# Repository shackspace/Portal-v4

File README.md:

Portal v4
=========

Portal v4 is the latest version of the shackspace [portal](https://github.com/shackspace/portal-v4). It controls access to shackspace through the ssh keys of the key members. Portal v4 is a more enhanced version and makes use of the Rasperry Pis GPIO pins. Also all python scripts are now updated from python 2.x to python 3.x.

Documentation for the setup is in `doc/setup.md`. The hardware setup is described in 'doc/hardware.md'

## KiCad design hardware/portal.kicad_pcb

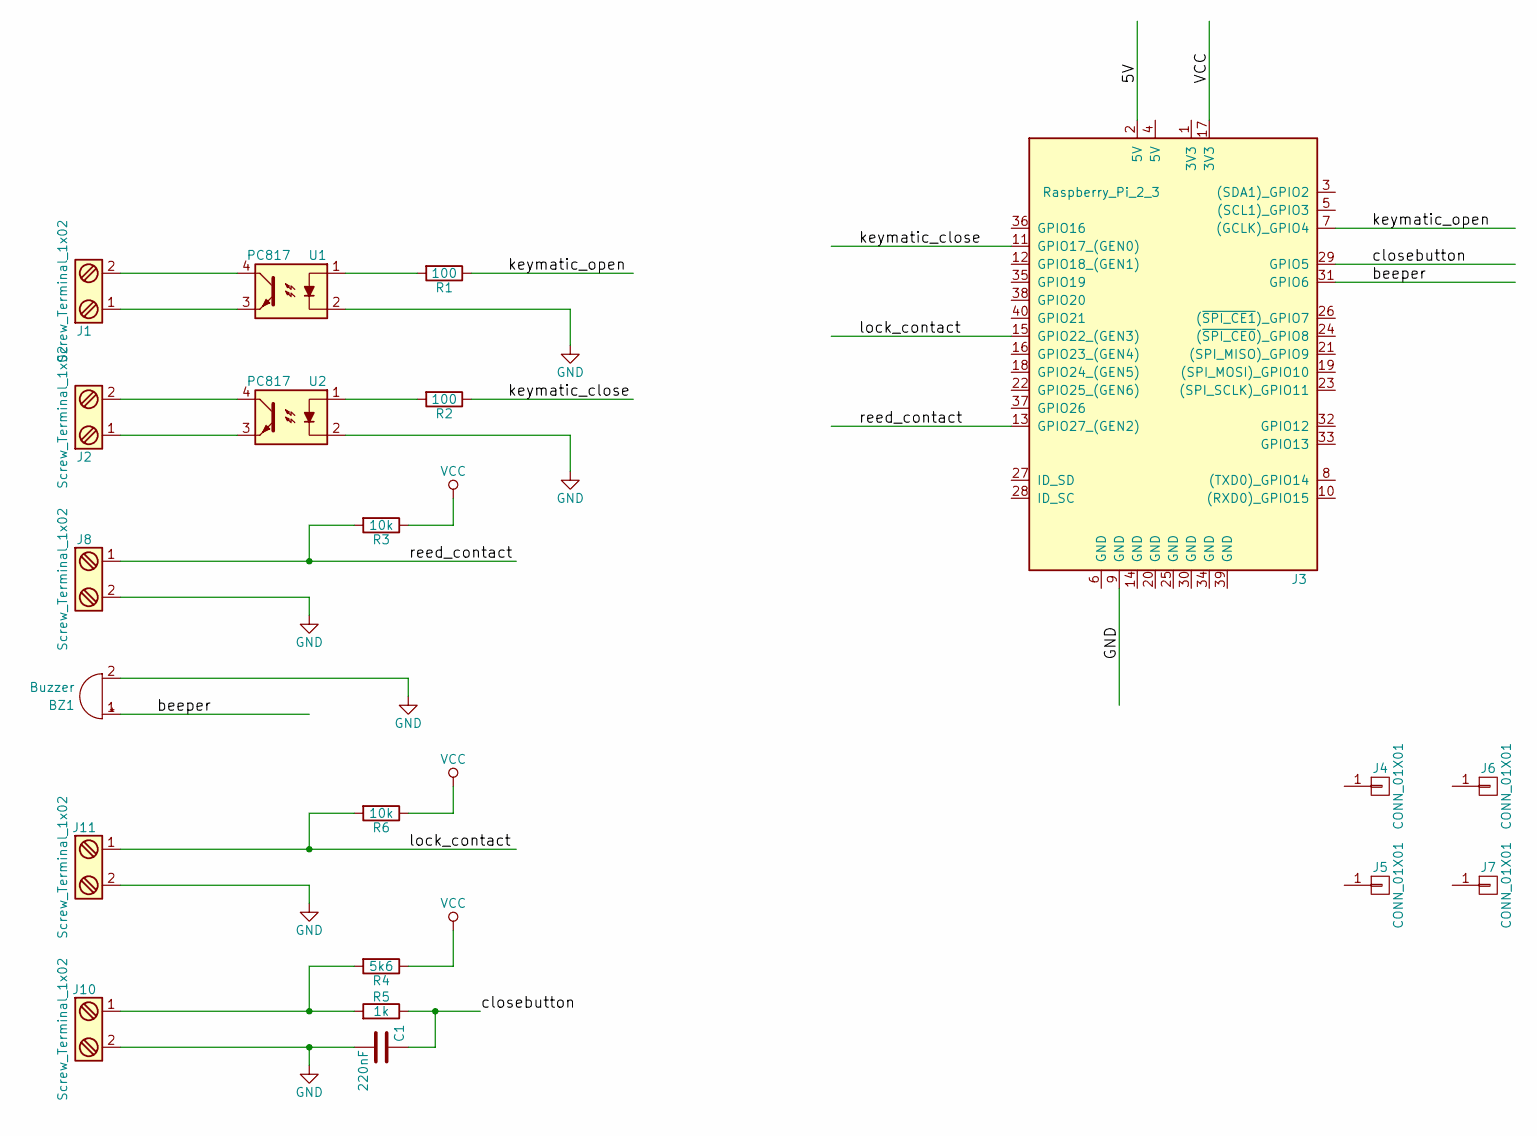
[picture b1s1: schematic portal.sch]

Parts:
BZ1: Buzzer; MagneticBuzzer_ProSignal_ABT-410-RC
C1: 220nF; C_0805_HandSoldering
J1, J2, J8, J10, J11: Screw_Terminal_1x02; SCREWTERMINAL-5MM-2
J3: Raspberry_Pi_2_3; Socket_Strip_Straight_2x20_Pitch2.54mm
J4, J5, J6, J7: CONN_01X01; MountingHole_2.7mm_M2.5
R1, R2: 100; R_0805_HandSoldering
R3, R6: 10k; R_0805_HandSoldering
R4: 5k6; R_0805_HandSoldering
R5: 1k; R_0805_HandSoldering
U1, U2: PC817; DIP-4_W7.62mm

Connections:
/5V: J3.2 (5V)
/beeper: BZ1.1 (-), J3.31 (GPIO6)
/closebutton: C1.1, J3.29 (GPIO5), R5.1
/keymatic_close: J3.11 (GPIO17_(GEN0)), R2.1
/keymatic_open: J3.7 ((GCLK)_GPIO4), R1.1
/lock_contact: J3.15 (GPIO22_(GEN3)), J11.1, R6.2
/reed_contact: J3.13 (GPIO27_(GEN2)), J8.1, R3.2
GND: BZ1.2 (+), C1.2, J3.9 (GND), J8.2, J10.2, J11.2, U1.2, U2.2
unnamed: J1.1, U1.3
unnamed: J1.2, U1.4
unnamed: J2.1, U2.3
unnamed: J2.2, U2.4
unnamed: J10.1, R4.2, R5.2
unnamed: R1.2, U1.1
unnamed: R2.2, U2.1
VCC: J3.17 (3V3), R3.1, R4.1, R6.1

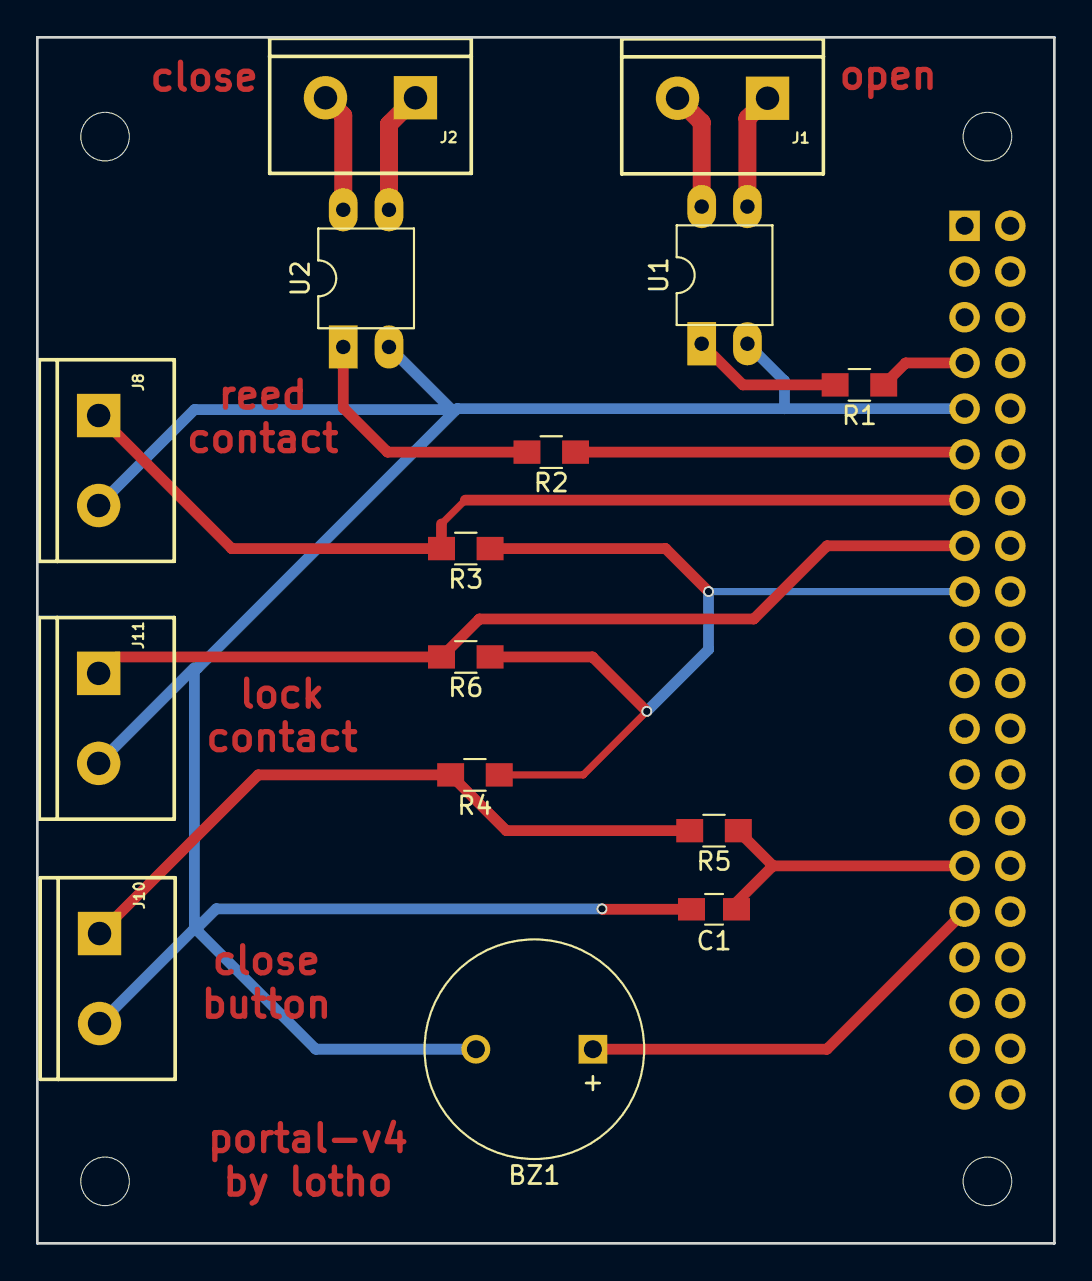
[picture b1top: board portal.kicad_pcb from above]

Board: 2 copper layers, 56.5 x 67.0 mm, 20 parts (1 on the bottom side), 15 nets.

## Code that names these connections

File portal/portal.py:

#!/usr/bin/env python3
# -*- coding:utf-8 -*-

import time
import sys
import os
import grp
import pwd
import datetime
import argparse

import RPi.GPIO as GPIO

GPIO.setmode(GPIO.BOARD)

GPIO.setwarnings(False)

DOOR_STATE_PIN = 13
DOOR_LOCK_STATE_PIN = 15
#CLOSEBUTTON_PIN = 29

BUZZER_PIN = 31
KEYMATIC_CLOSE_PIN = 11
KEYMATIC_OPEN_PIN = 7

#GPIO.setup(CLOSEBUTTON_PIN, GPIO.IN, pull_up_down=GPIO.PUD_DOWN)
GPIO.setup(DOOR_STATE_PIN, GPIO.IN, pull_up_down=GPIO.PUD_DOWN)
GPIO.setup(DOOR_LOCK_STATE_PIN, GPIO.IN, pull_up_down=GPIO.PUD_DOWN)

GPIO.setup(KEYMATIC_CLOSE_PIN, GPIO.OUT)
GPIO.setup(KEYMATIC_OPEN_PIN, GPIO.OUT)
GPIO.setup(BUZZER_PIN, GPIO.OUT)

GPIO.output(KEYMATIC_CLOSE_PIN, 0)
GPIO.output(KEYMATIC_OPEN_PIN, 0)
GPIO.output(BUZZER_PIN, 0)

LOGFILE = '/var/log/portal/portal.log'
LOCKFILE = '/var/run/lock/portal.lock'
STATUSFILE = '/var/log/portal/keyholder'
SERTIMEOUT = 1

LOGLEVEL = 2


class Portal():
    """
    Generic docstring
    """

    def __enter__(self):
        """Generic docstring"""
        return self

    def __exit__(self, type, value, traceback):
        """Generic docstring"""
        # self.serial.__exit__(type, value, traceback)

    def open_portal(self):
        """
        Open the door
        """
        for _ in range(3):
            print("opening keymatic")
            GPIO.output(KEYMATIC_OPEN_PIN, GPIO.HIGH)
            time.sleep(1)
            GPIO.output(KEYMATIC_OPEN_PIN, GPIO.LOW)
            time.sleep(5)
            if self.is_reed_open(15):
                self.beep_success()
                return
            self.beep_fail()

    def is_reed_open(self, timeout=0):
        """
        Generic docstring
        """
        status = GPIO.input(DOOR_LOCK_STATE_PIN)
        for _ in range(timeout):
            status = GPIO.input(DOOR_LOCK_STATE_PIN)
            log("door lock status: " + str(status), 2)
            if status:
                return True
            time.sleep(1)
        return status

    def is_reed_closed(self, timeout=0):
        """Generic docstring"""
        status = GPIO.input(DOOR_LOCK_STATE_PIN)
        for _ in range(timeout):
            status = GPIO.input(DOOR_LOCK_STATE_PIN)
            log("door lock status: " + str(status), 2)
            if not status:
                return True
            time.sleep(1)

        return not status

    def is_door_button_open(self):
        """Generic docstring"""
        return GPIO.input(DOOR_STATE_PIN)

    def close_door(self):
        """Generic docstring"""
        log("closing keymatic", 2)
        GPIO.output(KEYMATIC_CLOSE_PIN, GPIO.HIGH)
        time.sleep(1)
        GPIO.output(KEYMATIC_CLOSE_PIN, GPIO.LOW)

    def close_portal(self):
        """Generic docstring"""
        for _ in range(30):
            self.beep(.5)
            if self.is_door_button_open() == 0:
                log("door closed", 2)
                time.sleep(.5)
                GPIO.output(KEYMATIC_CLOSE_PIN, GPIO.HIGH)
                time.sleep(1)
                GPIO.output(KEYMATIC_CLOSE_PIN, GPIO.LOW)
                if self.is_reed_closed(15):
                    self.beep_success()
                    update_keyholder("No Keyholder")
                    return
                else:
                    break
            log("door still open", 2)
            time.sleep(0.5)
        self.alarm()

    def alarm(self):
        """
        Generic docstring
        """
        log("door close failed")
        self.beep_alarm()

    def beep(self, duration=0.2):
        """
        Generic docstring
        """
        GPIO.output(BUZZER_PIN, GPIO.HIGH)
        time.sleep(duration)
        GPIO.output(BUZZER_PIN, GPIO.LOW)

    def beep_alarm(self):
        """
        Generic docstring
        """
        for _ in range(30):
            self.beep(0.1)
            time.sleep(0.1)

    def beep_success(self):
        """
        Generic docstring
        """
        for _ in range(2):
            self.beep(0.2)
            time.sleep(0.2)

    def beep_fail(self):
        """
        Generic docstring
        """
        self.beep(1)


class Lockfile():
    """Generic docstring"""
    def __init__(self, lockfile):
        """Generic docstring"""
        self.lockfile = lockfile
        self.create_lock()

    def __enter__(self):
        """Generic docstring"""
        return self

    def __exit__(self, type, value, traceback):
        """Generic docstring"""
        self.remove_lock()

    def create_lock(self):
        """
        create a lockfile
        """
        if os.path.isfile(LOCKFILE):
            fp = open(self.lockfile, 'r')
            content = fp.read()
            content.strip()
            if self.lockpid_running(content):
                log('Could not lock open job, locked by %s' % content)
                sys.exit(1)
            else:
                log("Removing lockfile as %s isn't running anymore" % content, 2)
                self.remove_lock()
        with open(self.lockfile, 'w') as fp:
            fp.write(str(os.getpid()))

    def remove_lock(self):
        """
        remove the lock file
        """
        try:
            os.remove(self.lockfile)
        except OSError:
            log("Couldn't remove lock file: %s" % self.lockfile)

    def lockpid_running(self, pid):
        """
        check if pid is running
        """
        try:
            os.kill(int(pid), 0)
        except OSError:
            return False
        else:
            return True


def main():
    """Generic docstring"""
    motd()
    parser = get_option_parser()

    options = parser.parse_args()

    with Lockfile(LOCKFILE):
        with Portal() as portal:

            portal.beep(0.1)
            if options.action == 'open':
                msg = 'Door opened by: %s (ID: %s)' % (options.name, options.serial)
                log(msg)
                if options.nick:
                    update_keyholder(options.nick)
                else:
                    name = options.name
                    name = name.split(' ')
                    name[0] = name[0][:3]
                    if len(name) > 1:
                        name[len(name) - 1] = name[1][:1]
                    name = ' '.join(name)
                    update_keyholder(name)
                portal.open_portal()
            if options.action == 'close':
                msg = 'Door closed by: %s (ID: %s)' % (options.name, options.serial)
                log(msg)
                portal.close_portal()


def motd():
    """Generic docstring"""
    with open('/opt/Portal-v4/portal/motd.txt', 'r') as f:
        for line in f.readlines():
            print(line.rstrip('\n'))


def log(message, level=1):
    """Generic docstring"""
    if level > LOGLEVEL:
        return
    timestamp = datetime.datetime.now()
    message = str(timestamp) + ':\t' + message
    print(message)
    f = open(LOGFILE, 'a')
    f.write(message + "\n")
    f.close()


def check_options(options):
    """Generic docstring"""
    if not options.serial:
        print('Please provide a serial')
        sys.exit(1)
    if not options.name:
        print('Please provide a name')
        sys.exit(1)
    if not options.action:
        print('Please specify a action (open|close)')
        sys.exit(1)

    valid_actions = ['open', 'close']
    if options.action not in valid_actions:
        print('Option must be open or close')
        sys.exit(1)


def update_keyholder(name):
    """
    update the status file with the current keyholder
    """
    with open(STATUSFILE, 'w') as f:
        f.write(name)
        gid = grp.getgrnam("portal").gr_gid
        uid = uid = pwd.getpwnam("open").pw_uid


def get_option_parser():
    """
    create Argument Parser object and add options
    """
    parser = argparse.ArgumentParser(description='Description')
    parser.add_argument('-s', '--serial',
                        dest='serial',
                        help='members ID',
                        required=True)
    parser.add_argument('-n', '--name',
                        dest='name',
                        help='keymembers name name_surname',
                        required=True)
    parser.add_argument('--nick',
                        dest='nick',
                        help='OPT: members nickname',
                        required=True)
    parser.add_argument('-a', '--action',
                        dest='action',
                        help='open|close',
                        required=True)
    parser.add_argument('-l', '--last',
                        dest='last',
                        help='OPT: last valid day of the key')
    parser.add_argument('-f', '--first',
                        dest='first',
                        help='OPT: first valid day of the key')
    return parser


if __name__ == '__main__':
    main()

GPIO.cleanup()

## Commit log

2018-05-04 init
2018-05-10 Added debouncing to the PCB and widened the traces
2018-05-13 using a portal version independent path
2018-12-03 Keyholder removal after successful closing
